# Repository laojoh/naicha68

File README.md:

# naicha68

A keyboard dreamt up and put into solid design by @deltea and @laojoh.

We are both into keyboards, so we wanted to make a keyboard that satisfies both of our wants. Also, keyboards are so cool!
To use our project, you can connect the keyboard through bluetooth to your computer, and type away!

[Check out the Onshape CAD here!](https://cad.onshape.com/documents/295e0b7142940424b9052f56/w/e19706a5ab64c98e31915beb/e/17c8e54cfbba57455b125845)

This keyboard uses the ZMK firmware.

This is the custom layout we chose for the keyboard (made with [keyboard-layout-editor.com](https://www.keyboard-layout-editor.com/#/)):

## PCB Renders

## Case

## PCB

|Name                                                                                  |Quantity|Link/File                                                                                                                                                                                                                                                                                                                                                                                                                                                                                                                                                                                                                                                         |Price / unit|Total Price|Stock          |Notes|
|--------------------------------------------------------------------------------------|--------|------------------------------------------------------------------------------------------------------------------------------------------------------------------------------------------------------------------------------------------------------------------------------------------------------------------------------------------------------------------------------------------------------------------------------------------------------------------------------------------------------------------------------------------------------------------------------------------------------------------------------------------------------------------|------------|-----------|---------------|-----|
|Totals                                                                                |10      |                                                                                                                                                                                                                                                                                                                                                                                                                                                                                                                                                                                                                                                                  |            |$177.93    |               |     |
|Case                                                                                  |1       |                                                                                                                                                                                                                                                                                                                                                                                                                                                                                                                                                                                                                                                                  |$0.00       |$0.00      |Not yet started|     |
|Plate                                                                                 |1       |                                                                                                                                                                                                                                                                                                                                                                                                                                                                                                                                                                                                                                                                  |            |$1.00      |Not yet started|     |
|Seeed Studio XIAO nRF52840                                                            |1       |XIAO nRF52840 - Tiny Arduino Board Supports Bluetooth 5.0                                                                                                                                                                                                                                                                                                                                                                                                                                                                                                                                                                                                         |$10.00      |$10.00     |Not yet started|     |
|AliExpress Display                                                                    |1       |https://www.aliexpress.us/item/3256804386173217.html?spm=a2g0o.productlist.main.30.20eeHJVkHJVk5m&algo_pvid=93673717-29b3-4744-ae00-dcf9256ced0e&algo_exp_id=93673717-29b3-4744-ae00-dcf9256ced0e-29&pdp_ext_f=%7B"order"%3A"1219"%2C"eval"%3A"1"%2C"fromPage"%3A"search"%7D&pdp_npi=6%40dis%21USD%212.10%210.99%21%21%212.10%210.99%21%402103212317701384394338331e3e1c%2112000029674573173%21sea%21US%216679426554%21ABX%211%210%21n_tag%3A-29910%3Bd%3A888201d9%3Bm03_new_user%3A-29895%3BpisId%3A5000000197847477&curPageLogUid=msSzhMdeEBVq&utparam-url=scene%3Asearch%7Cquery_from%3A%7Cx_object_id%3A1005004572487969%7C_p_origin_prod%3A#nav-specification|$7.36       |$7.36      |Not yet started|     |
|Kailh Hot-swap PCB Socket Hot Plug for Mechanical Keyboard DIY PCB Accessories (70pcs)|1       |https://www.amazon.com/VEGNRSOT-Hot-swap-Mechanical-Keyboard-Accessories/dp/B0CZ79H1D9?sr=1-2&th=1                                                                                                                                                                                                                                                                                                                                                                                                                                                                                                                                                                |$10.00      |$10.00     |Not yet started|     |
|PCB                                                                                   |1       |                                                                                                                                                                                                                                                                                                                                                                                                                                                                                                                                                                                                                                                                  |$110.58     |$110.58    |Not yet started|     |
|Magnets                                                                               |1       |Amazon.com: 40pcs Small Round Refrigerator Magnets - Mini Craft Magnets for Whiteboard, Dry Erase Board in Home, Kitchen                                                                                                                                                                                                                                                                                                                                                                                                                                                                                                                                          |$6.99       |$6.99      |Not yet started|     |
|Gasket Tape                                                                           |1       |https://www.amazon.com/ToLanbbt-Stripping-Adhesive-Insulation-Weatherproof/dp/B0DSBHMPFT?sr=8-11                                                                                                                                                                                                                                                                                                                                                                                                                                                                                                                                                                  |$12.00      |$12.00     |Not yet started|     |
|AliExpress Lithium Battery                                                            |1       |https://www.aliexpress.us/item/3256809404408618.html?mp=1&pdp_npi=6@dis!USD!USD%2020.86!USD%200.99!!USD%200.99!!!@2103123917715219546135171ea124!12000049557506745!ct!US!6679426554!!1!0!&gatewayAdapt=glo2usa                                                                                                                                                                                                                                                                                                                                                                                                                                                    |$1.00       |$1.00      |Not yet started|     |

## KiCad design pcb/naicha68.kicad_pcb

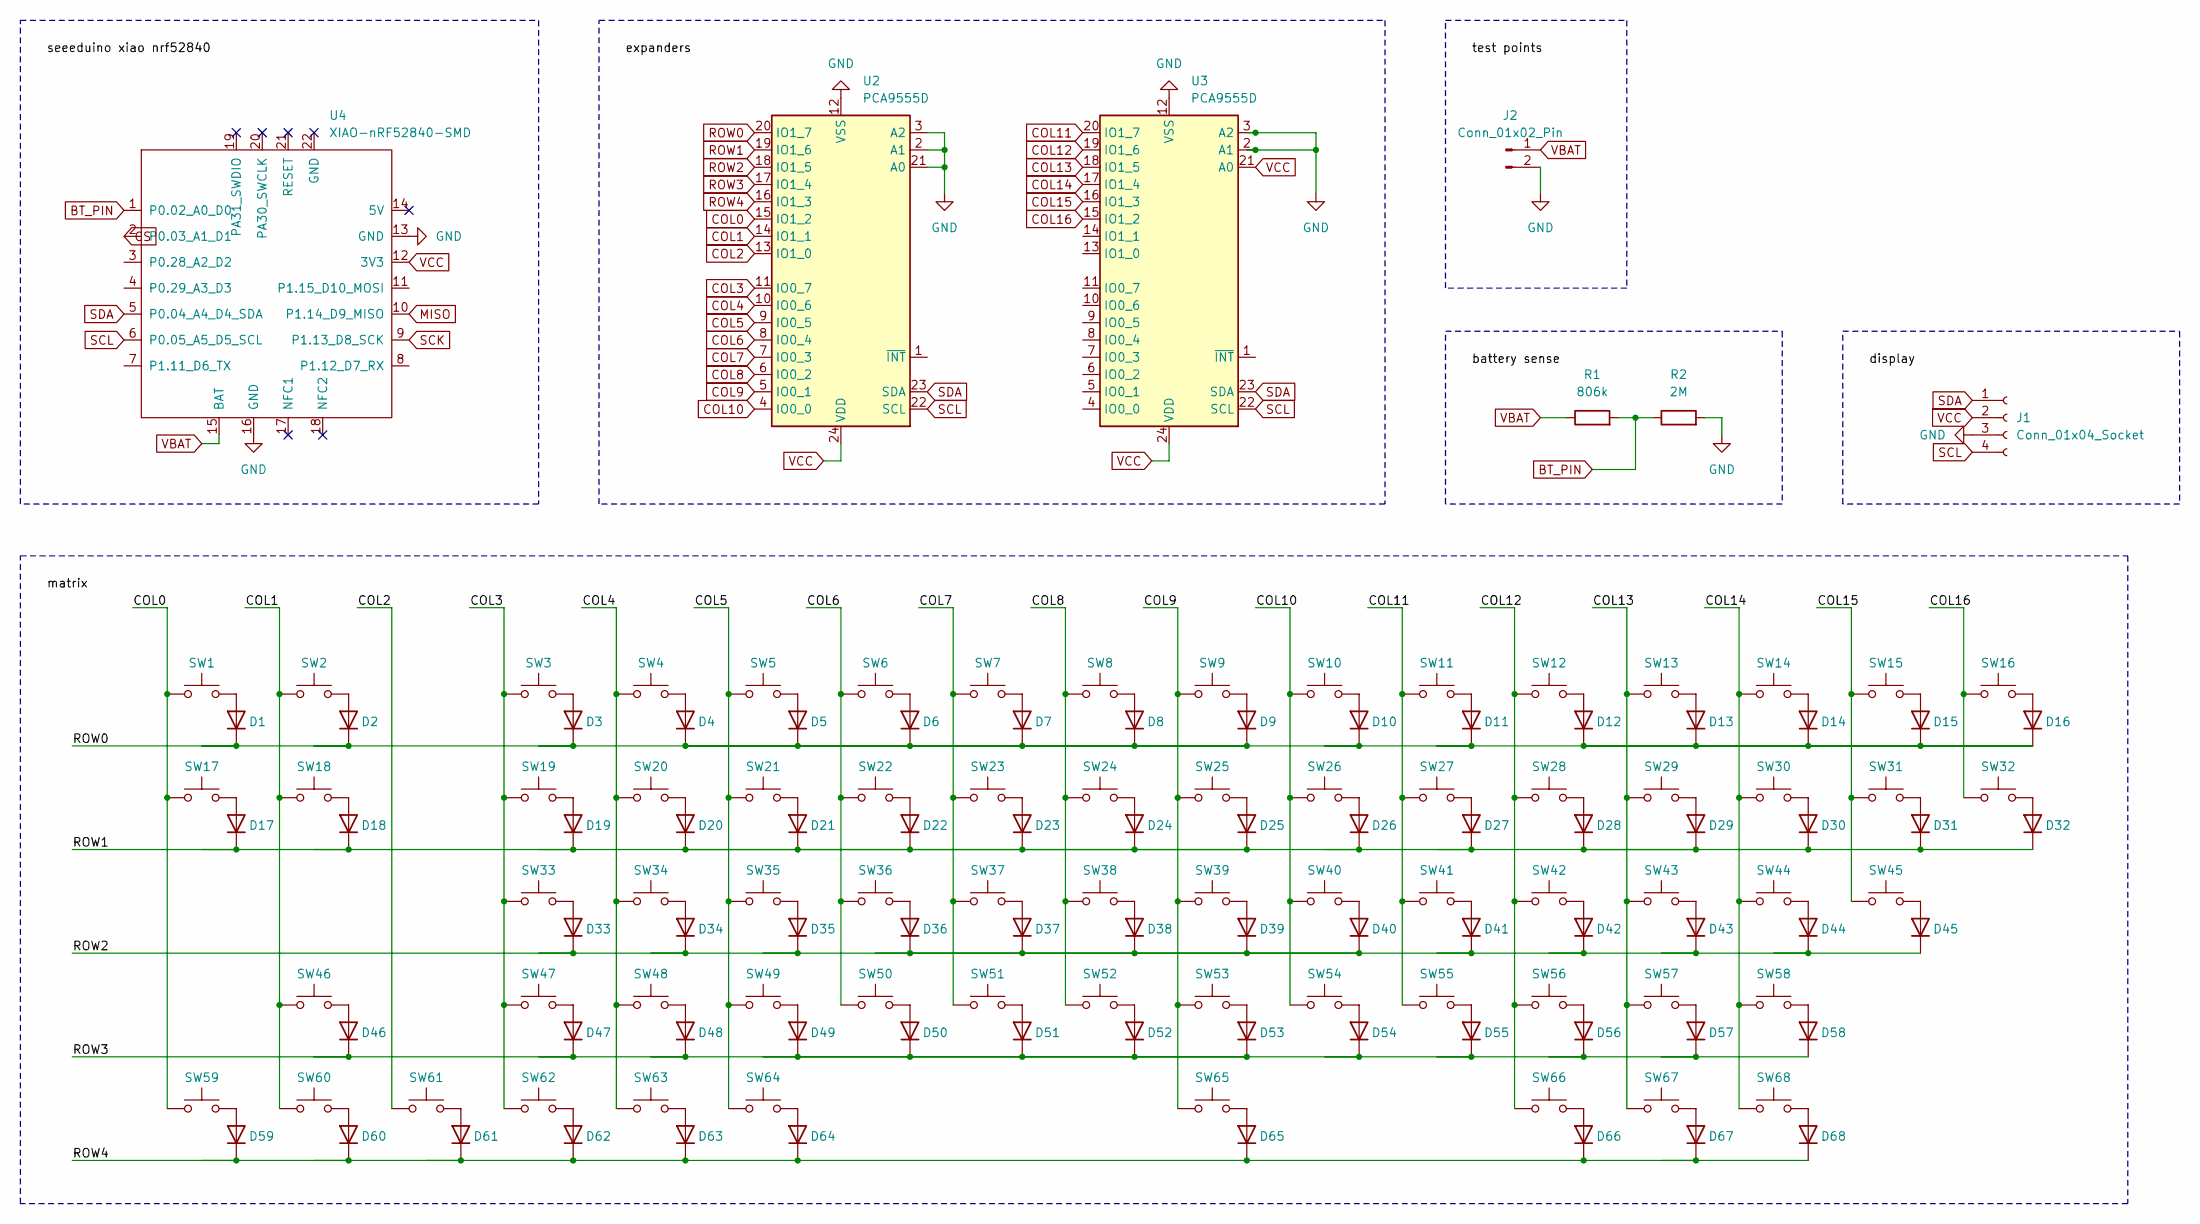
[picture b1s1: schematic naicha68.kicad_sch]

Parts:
D1, D2, D3, D4, D5, D6, D7, D8, D9, D10, D11, D12, D13, D14, D15, D16, D17, D18, D19, D20, D21, D22, D23, D24, D25, D26, D27, D28, D29, D30, D31, D32, D33, D34, D35, D36, D37, D38, D39, D40, D41, D42, D43, D44, D45, D46, D47, D48, D49, D50, D51, D52, D53, D54, D55, D56, D57, D58, D59, D60, D61, D62, D63, D64, D65, D66, D67, D68: D; D_SOD-123
J1: Conn_01x04_Socket; PinHeader_1x04_P2.54mm_Vertical
J2: Conn_01x02_Pin; JST_JWPF_B02B-JWPF-SK-R_1x02_P2.00mm_Vertical
R1: 806k; R_0805_2012Metric
R2: 2M; R_0805_2012Metric
SW1, SW2, SW3, SW4, SW5, SW6, SW7, SW8, SW9, SW10, SW11, SW12, SW13, SW14, SW15, SW16, SW17, SW18, SW19, SW20, SW21, SW22, SW23, SW24, SW25, SW26, SW27, SW28, SW29, SW30, SW31, SW32, SW33, SW34, SW35, SW36, SW37, SW38, SW39, SW40, SW41, SW42, SW43, SW44, SW45, SW46, SW47, SW48, SW49, SW50, SW51, SW52, SW53, SW54, SW55, SW56, SW57, SW58, SW59, SW60, SW61, SW62, SW63, SW64, SW65, SW66, SW67, SW68: SW_Push; SW_MX_HS_CPG151101S11_1u
U2, U3: PCA9555D; SOIC-24W_7.5x15.4mm_P1.27mm
U4: XIAO-nRF52840-SMD; modified-XIAO-nRF52840-SMD

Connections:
BT_PIN: R1.2, R2.1, U4.1 (P0.02_A0_D0)
COL0: SW1.1, SW17.1, SW59.1, U2.15 (IO1_2)
COL1: SW2.1, SW18.1, SW46.1, SW60.1, U2.14 (IO1_1)
COL2: SW61.1, U2.13 (IO1_0)
COL3: SW3.1, SW19.1, SW33.1, SW47.1, SW62.1, U2.11 (IO0_7)
COL4: SW4.1, SW20.1, SW34.1, SW48.1, SW63.1, U2.10 (IO0_6)
COL5: SW5.1, SW21.1, SW35.1, SW49.1, SW64.1, U2.9 (IO0_5)
COL6: SW6.1, SW22.1, SW36.1, SW50.1, U2.8 (IO0_4)
COL7: SW7.1, SW23.1, SW37.1, SW51.1, U2.7 (IO0_3)
COL8: SW8.1, SW24.1, SW38.1, SW52.1, U2.6 (IO0_2)
COL9: SW9.1, SW25.1, SW39.1, SW53.1, SW65.1, U2.5 (IO0_1)
COL10: SW10.1, SW26.1, SW40.1, SW54.1, U2.4 (IO0_0)
COL11: SW11.1, SW27.1, SW41.1, SW55.1, U3.20 (IO1_7)
COL12: SW12.1, SW28.1, SW42.1, SW56.1, SW66.1, U3.19 (IO1_6)
COL13: SW13.1, SW29.1, SW43.1, SW57.1, SW67.1, U3.18 (IO1_5)
COL14: SW14.1, SW30.1, SW44.1, SW58.1, SW68.1, U3.17 (IO1_4)
COL15: SW15.1, SW31.1, SW45.1, U3.16 (IO1_3)
COL16: SW16.1, SW32.1, U3.15 (IO1_2)
CS: U4.2 (P0.03_A1_D1)
GND: J1.3, J2.2, R2.2, U2.2 (A1), U2.3 (A2), U2.12 (VSS), U2.21 (A0), U3.2 (A1), U3.3 (A2), U3.12 (VSS), U4.13 (GND), U4.16 (GND)
MISO: U4.10 (P1.14_D9_MISO)
unnamed: D1.2 (A), SW1.2
unnamed: D2.2 (A), SW2.2
unnamed: D3.2 (A), SW3.2
unnamed: D4.2 (A), SW4.2
unnamed: D5.2 (A), SW5.2
unnamed: D6.2 (A), SW6.2
unnamed: D7.2 (A), SW7.2
unnamed: D8.2 (A), SW8.2
unnamed: D9.2 (A), SW9.2
unnamed: D10.2 (A), SW10.2
unnamed: D11.2 (A), SW11.2
unnamed: D12.2 (A), SW12.2
unnamed: D13.2 (A), SW13.2
unnamed: D14.2 (A), SW14.2
unnamed: D15.2 (A), SW15.2
unnamed: D16.2 (A), SW16.2
unnamed: D17.2 (A), SW17.2
unnamed: D18.2 (A), SW18.2
unnamed: D19.2 (A), SW19.2
unnamed: D20.2 (A), SW20.2
unnamed: D21.2 (A), SW21.2
unnamed: D22.2 (A), SW22.2
unnamed: D23.2 (A), SW23.2
unnamed: D24.2 (A), SW24.2
unnamed: D25.2 (A), SW25.2
unnamed: D26.2 (A), SW26.2
unnamed: D27.2 (A), SW27.2
unnamed: D28.2 (A), SW28.2
unnamed: D29.2 (A), SW29.2
unnamed: D30.2 (A), SW30.2
unnamed: D31.2 (A), SW31.2
unnamed: D32.2 (A), SW32.2
unnamed: D33.2 (A), SW33.2
unnamed: D34.2 (A), SW34.2
unnamed: D35.2 (A), SW35.2
unnamed: D36.2 (A), SW36.2
unnamed: D37.2 (A), SW37.2
unnamed: D38.2 (A), SW38.2
unnamed: D39.2 (A), SW39.2
unnamed: D40.2 (A), SW40.2
unnamed: D41.2 (A), SW41.2
unnamed: D42.2 (A), SW42.2
unnamed: D43.2 (A), SW43.2
unnamed: D44.2 (A), SW44.2
unnamed: D45.2 (A), SW45.2
unnamed: D46.2 (A), SW46.2
unnamed: D47.2 (A), SW47.2
unnamed: D48.2 (A), SW48.2
unnamed: D49.2 (A), SW49.2
unnamed: D50.2 (A), SW50.2
unnamed: D51.2 (A), SW51.2
unnamed: D52.2 (A), SW52.2
unnamed: D53.2 (A), SW53.2
unnamed: D54.2 (A), SW54.2
unnamed: D55.2 (A), SW55.2
unnamed: D56.2 (A), SW56.2
unnamed: D57.2 (A), SW57.2
unnamed: D58.2 (A), SW58.2
unnamed: D59.2 (A), SW59.2
unnamed: D60.2 (A), SW60.2
unnamed: D61.2 (A), SW61.2
unnamed: D62.2 (A), SW62.2
unnamed: D63.2 (A), SW63.2
unnamed: D64.2 (A), SW64.2
unnamed: D65.2 (A), SW65.2
unnamed: D66.2 (A), SW66.2
unnamed: D67.2 (A), SW67.2
unnamed: D68.2 (A), SW68.2
ROW0: D1.1 (K), D2.1 (K), D3.1 (K), D4.1 (K), D5.1 (K), D6.1 (K), D7.1 (K), D8.1 (K), D9.1 (K), D10.1 (K), D11.1 (K), D12.1 (K), D13.1 (K), D14.1 (K), D15.1 (K), D16.1 (K), U2.20 (IO1_7)
ROW1: D17.1 (K), D18.1 (K), D19.1 (K), D20.1 (K), D21.1 (K), D22.1 (K), D23.1 (K), D24.1 (K), D25.1 (K), D26.1 (K), D27.1 (K), D28.1 (K), D29.1 (K), D30.1 (K), D31.1 (K), D32.1 (K), U2.19 (IO1_6)
ROW2: D33.1 (K), D34.1 (K), D35.1 (K), D36.1 (K), D37.1 (K), D38.1 (K), D39.1 (K), D40.1 (K), D41.1 (K), D42.1 (K), D43.1 (K), D44.1 (K), D45.1 (K), U2.18 (IO1_5)
ROW3: D46.1 (K), D47.1 (K), D48.1 (K), D49.1 (K), D50.1 (K), D51.1 (K), D52.1 (K), D53.1 (K), D54.1 (K), D55.1 (K), D56.1 (K), D57.1 (K), D58.1 (K), U2.17 (IO1_4)
ROW4: D59.1 (K), D60.1 (K), D61.1 (K), D62.1 (K), D63.1 (K), D64.1 (K), D65.1 (K), D66.1 (K), D67.1 (K), D68.1 (K), U2.16 (IO1_3)
SCK: U4.9 (P1.13_D8_SCK)
SCL: J1.4, U2.22 (SCL), U3.22 (SCL), U4.6 (P0.05_A5_D5_SCL)
SDA: J1.1, U2.23 (SDA), U3.23 (SDA), U4.5 (P0.04_A4_D4_SDA)
VBAT: J2.1, R1.1, U4.15 (BAT)
VCC: J1.2, U2.24 (VDD), U3.21 (A0), U3.24 (VDD), U4.12 (3V3)

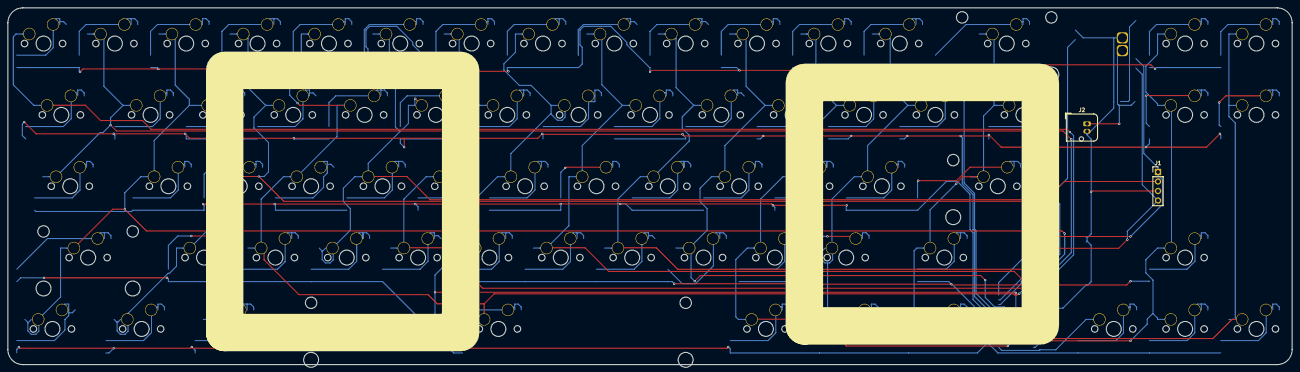
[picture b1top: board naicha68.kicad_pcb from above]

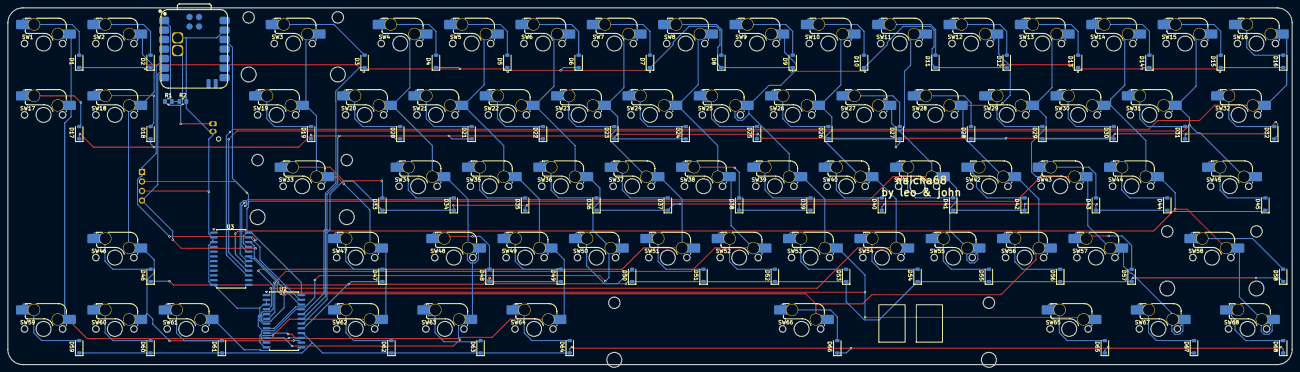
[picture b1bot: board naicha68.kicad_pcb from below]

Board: 2 copper layers, 342.9 x 95.2 mm, 147 parts (141 on the bottom side), 96 nets.

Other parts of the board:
S1: STAB_MX_2u
S2, S3: STAB_MX_2.25u
S4: STAB_MX_6.25u

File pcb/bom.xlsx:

Designator | Footprint | Comment
J2 | JST_JWPF_B02B-JWPF-SK-R_1x02_P2.00mm_Vertical | Conn_01x02_Pin
J1 | PinHeader_1x04_P2.54mm_Vertical | Conn_01x04_Socket
SW43,SW38,SW11,SW65,SW16,SW45,SW57,SW9,SW21,SW59,SW22,SW28,SW34,SW5,SW48,SW53,S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 | SW_MX_HS_CPG151101S11_1u | SW_Push
D43,D40,D45,D29,D33,D36,D18,D17,D56,D13,D3,D22,D31,D52,D9,D41,D12,D51,D21,D5,D7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 | D_SOD-123 | D
U2,U3 | SOIC-24W_7.5x15.4mm_P1.27mm | PCA9555D
R1 | R_0805_2012Metric | 806k
R2 | R_0805_2012Metric | 2M
U4 | modified-XIAO-nRF52840-SMD | XIAO-nRF52840-SMD

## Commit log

2026-01-22 upload bom
2026-01-22 upload kicad_pro file
2026-01-22 add keyboard layout reference
2026-01-22 upload some photos
2026-01-22 add bom to readme
2026-01-22 add headers
2026-01-29 update readme with bom table and description
2026-01-29 new pcb upload
2026-02-04 new pcb udpates
2026-02-23 Include CAD link in README
    Added a link to the CAD document for the keyboard project.
2026-02-23 added STEP file
2026-02-23 add new kicad files
2026-02-23 update bom
2026-03-06 add screenshots of case cad
2026-03-06 add keyboard layotu to readme
2026-03-06 move some stuff around
2026-03-20 organize folders and files
